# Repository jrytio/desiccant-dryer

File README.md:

# desiccant-dryer

ESPHome firmware for an ESP32 replacement of the Azco VMD-08 desiccant
air dryer control board, on a SparkFun ESP32-S2 Thing Plus or a SparkFun
Thing Plus ESP32-C6 (same sockets and wiring, one image each). Swaps packs
on measured humidity and pack
temperature instead of a fixed timer. See `CLAUDE.md` for decisions,
`docs/hardware.md` for wiring and BOM, `docs/control-logic.md` for the
state machine, `docs/virtual-testing.md` for testing without hardware,
`docs/host-preview.md` for the display on your Mac,
`docs/releasing.md` for numbered production releases and updates through Home Assistant.

Three builds share `esphome/packages/base.yaml`:

| Build | File | Sensors | Runs on |
|---|---|---|---|
| Production | `esphome/desiccant-dryer.yaml`, `esphome/desiccant-dryer-c6.yaml` | SHT45 + 3× DS18B20 (`packages/hw-real.yaml`) | ESP32-S2, ESP32-C6 |
| Hardware test | `esphome/desiccant-dryer-hw-test.yaml`, `esphome/desiccant-dryer-hw-test-c6.yaml` | Same real sensors, dev credentials and OTA | ESP32-S2, ESP32-C6 |
| Virtual | `esphome/desiccant-dryer-virtual.yaml` | On-device plant model (`packages/hw-virtual.yaml`) | ESP32-S2, nothing attached |
| Host | `esphome/desiccant-dryer-host.yaml` | Same plant model | Your Mac, display in an SDL window |
| Screen scenarios | `esphome/desiccant-dryer-scenarios.yaml` | Fixed table of twelve screen states, no controller | Your Mac; `scripts/scenario-shots.sh` renders them to `docs/display/` |

```
cp esphome/secrets.yaml.example esphome/secrets.yaml   # fill in (test builds only)
esphome run esphome/desiccant-dryer-virtual.yaml       # bare board
esphome run esphome/desiccant-dryer.yaml               # real hardware; no secrets, WiFi set at flash time
esphome run esphome/desiccant-dryer-host.yaml          # no board; brew install sdl2 first
```

CI compiles all of these on every pull request. Pushing a `vX.Y.Z` tag
(`scripts/release.sh`) publishes the production build; owners install it
once over USB with web.esphome.io, and the unit then installs later
releases itself from the published manifest, on a 6 h poll, through the
`Firmware` update entity in Home Assistant. See `docs/releasing.md`,
which also records the accepted security trade-offs of that arrangement.

## Printed circuit board

`hardware/` holds a KiCad 10 design for two fab-assembled boards: a
controller board that takes the same Thing Plus sockets and pin map, with
keyed pluggable headers, and a mains board (fuse, relays, 120 VAC plug)
behind a routed slot, joined by a keyed 4-way link. Both are generated from
Python (`scripts/hardware.sh`), checked by ERC and DRC in CI, and not yet
built. Commands, CI and ordering are in
[`hardware/README.md`](hardware/README.md); BOM, pinouts and LEDs in
`docs/hardware.md`.

## License

Copyright (C) 2026 jrytio. Released under the GNU Affero General Public
License v3.0; see [`LICENSE`](LICENSE). If you run a modified version where
others interact with it over a network (the web server, the API), the AGPL requires you to offer them your source.

Exceptions: the vendor documents in `docs/datasheets/` belong to their
manufacturers and are not covered. Release firmware also contains ESPHome's
C++ runtime (MIT), ESP-IDF (Apache 2.0) and the Barlow and Inter fonts
(SIL Open Font License 1.1), each under its own license.

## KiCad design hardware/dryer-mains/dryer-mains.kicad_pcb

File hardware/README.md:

# Hardware: the controller and mains PCBs

Two boards, generated from `dryer_board/` (see `docs/superpowers/specs/2026-10-14-pcb-design-kicad-design.md`, and its "As built" section for where the boards differ from it):

- **`dryer-controller`** (85 × 70 mm, the controller space in the enclosure): the socketed Thing Plus, 24 V in, the 5 V module, the USB-pin switch, the three MOSFET stages, the sensor and display headers, and J_RLY, the link to the mains board.
- **`dryer-mains`** (45 × 70 mm, the mains space): the fuse, the two relays with their driver stages, the 120 VAC plug, and J_CTRL, the other end of the link. The mains zone sits behind a 2 mm routed slot with four gaps for the coil tracks. Both outlines are the reviewer's enclosure sizes; the corner mounting holes (4 mm in from each edge) and the USB-C overhang (3 mm past the controller's left edge) are assumptions awaiting his confirmation; the mains plug is a vertical header inside the outline since he reported a wall beside the mains space (docs/superpowers/specs/2026-10-15-pcb-two-board-split-design.md).

The link is a JST-XH 4-way, the protoboard harness's connector and pin order: **1 = 5 V, 2 = GND, 3 = heater A, 4 = heater B**, labelled beside both headers. Pin 1 is at the top of each header with the boards side by side (controller left, mains right). The cable is 1:1, XHP-4 housing to XHP-4 housing (a pre-made "XH 2.54" 4-pin female-female lead is the same thing: XH is 2.50 mm); keep it under 30 cm. The link's 2.5 mm pitch means no other plug on either board fits it. The SHT45 is not on either board: it plugs into the Thing Plus's own Qwiic connector with a Qwiic/STEMMA QT cable (docs/hardware.md "Header pinouts").

BOM, header pinouts, LEDs, clearances and the USB-pin budget are in `docs/hardware.md` ("Printed circuit board (rev A)"); revisions and the `pcb-*` release tag in `docs/releasing.md`.

    scripts/hardware.sh env       # where KiCad was found
    scripts/hardware.sh test      # unit tests (KiCad's Python)
    scripts/hardware.sh generate [--fresh] [board]   # schematic, project, board (keeps existing tracks)
    scripts/hardware.sh route [board] [passes]       # Freerouting 2.5.0 in Docker (default 50) reroutes the SELV nets from scratch; mains copper is mains.MAINS_TRACKS
    scripts/hardware.sh check [board]                # committed files match the model; ERC; DRC
    scripts/hardware.sh export [--no-docs] [board]   # fab files and renders to hardware/out/, review copies to docs/hardware/ (--no-docs skips the copy)

Every command runs over both boards unless one is named (`controller` or `mains`). Needs KiCad 10 (`brew install --cask kicad`) and Docker for `route`. No Java.

Do not use the KiCad GUI's "Update PCB from Schematic" on these boards: the footprints carry no schematic
path, so KiCad would treat every part as new or orphaned. The generator is the update path: change
`dryer_board/`, then `generate` (and `route` if the SELV connectivity changed). The local footprints
(`dryer:*`) live in `lib/dryer.pretty` and are copied into each project's `lib/` by `generate`; edit the
copy in `lib/`, not a project's.

## Ordering (JLCPCB)

`scripts/hardware.sh export` writes, for each board, `hardware/out/dryer-<board>-rev<N>-gerbers.zip`, `-bom.csv` and `-cpl.csv`. Order the two boards as two JLCPCB orders (or one order with two files if JLCPCB offers it); each has its own BOM and CPL.

1. Upload each board's gerber zip, BOM CSV and CPL CSV to JLCPCB.
2. Options: 2 layers, 1.6 mm, 1 oz copper, HASL lead-free, assembly on the top side.
3. Run JLCPCB's DFM analysis on the uploaded gerbers before paying.
4. In JLCPCB's placement preview, check every polarised and keyed part before paying. The CPL is already written for JLCPCB: each part's position is the centre of its pads (KiCad's own position file gives the footprint anchor, which is pin 1 on the connectors, sockets, relays, fuse holder, switch and U1, so those appeared shifted by half a body in the first upload on 2026-10-16), and the rotations carry the per-package corrections in `JLC_ROTATIONS` in `hardware/dryer_board/export.py` (pluggable headers and the XH links 180°, 1×N pin sockets and headers −90°, SOT-23 180°, electrolytics 180°, SMA diodes 180°, 0805 LEDs 180°; resistors, ceramics and the PPTC unchanged). The connector, socket, SOT-23 and electrolytic values match that preview; the SMA diodes, the LEDs, the direction of the pin-socket turn (pin 1 at the USB end), the relays, the fuse holder and the slide switch are set by analogy or left at KiCad's angle and must be confirmed in the preview. If one is off, change its entry in `JLC_ROTATIONS`, run `scripts/hardware.sh export`, re-upload the CPL and look again; do not fix it only in the browser, or the next export loses it. The flyback diodes D5 to D7 and the 24 V diodes D11 and D14 matter most: reversed, a flyback shorts its output when it switches on. JLCPCB's 3D review draws a flat box over the footprint for any part its library has no 3D model for; the fuse holder (XFCN PTF-76-B, C48603682) is one of them (seen 2026-10-16: JLCPCB's part page lists an EasyEDA footprint and no model). That is not an error: check the part in the 2D view instead (two pads 15 mm apart, 1.6 mm holes, body outline 24.4 × 9.4 mm, which is what XFCN's drawing gives) and that the BOM step matched it to C48603682 with through-hole assembly on.
5. The minimum order is five boards of each.
6. Every fab-fitted part carries its LCSC number in the BOM (`hardware/dryer_board/controller.py` and `mains.py`; each part's description says basic or extended). JLCPCB charges a per-part loading fee for each extended part: the relays, the MOSFETs, the electrolytics, the PPTC, the fuse holder, the headers and sockets, the two XH link headers and the switch.
7. **U1 (the 5 V module, controller board) is hand-fitted.** It is in the BOM with no LCSC number, so deselect it in JLCPCB's BOM check. The footprint is drawn for the TRACO TSR 1-2450 (Mouser 495-TSR-1-2450). The Amazon-listed "AOTUPASION TSR 1-2450" (B0GTTJ4PNX) fits it mechanically: 11.5 × 7.5 × 10 mm body inside the footprint's 11.7 × 7.6 outline, three SIP pins on the 2.54 mm pitch, and the pin-1 dot at the same end as TRACO's drawing. The listing does not state its pinout and the label carries no TRACO logo, so **before soldering one, power it on the bench: current-limited 12 V on pin 1 (+) and pin 2 (GND), expect 5 V on pin 3** (docs/board-continuity-check.md, PCB item 0). A MornSun K7805-1000R3 from another distributor also fits (same pinout).
8. **F1 (the fuse holder, mains board) is fab-fitted**: the XFCN PTF-76-B covered holder (LCSC C48603682, 15 mm pitch, UL 250 VAC 20 A), the single-board rev A's choice. The covered 5 × 20 mm holders on hand (Amazon B0FCS5MK1Y, the BLX-A moulding; the reviewer confirmed their pitch at about 22 mm on 2026-10-15, after a first reading of 12.5 mm from the listing's picture) are **not fitted**: with mains copper 1 mm from the slot, their 25.8 mm body would run from x 10.35 to 36.15 and into the vertical plug (strip, slot, clearance, holder and the plug's body add up to 45.6 mm across the 45 mm board; 1 mm over against the plug's courtyard). The `Fuseholder_5x20mm_Covered_P22.50mm_Slot` footprint stays in `lib/dryer.pretty` for a right-angle-plug layout, where they fit. The 5 × 20 mm fuse itself (T 3.15 A) is bought separately. First-article note: the plug's pin-1 wires leave 2 to 4 mm from the holder's lift-off cap, so changing the fuse may need the plug pulled first (unverified until a board is built).
9. The mating plugs for the pluggable headers, and the link cable, are not on the boards. Order them as loose parts (LCSC numbers; DORABO screw plugs, green):

   | Header | Plug | LCSC |
   |---|---|---|
   | J_MAINS (8-pin 5.08 mm, mains board; the header is the vertical DB2EV-5.08-8P-GN, C395787, since the reviewer reported a wall beside the mains space) | DB2EK-5.08-8P-GN-S | C395791 |
   | J_LOADS (6-pin 5.08 mm, controller) | DB2EK-5.08-6P-GN-S | C395774 |
   | J_24V (2-pin 5.08 mm, controller) | DB2EK-5.08-2P-GN-S | C395732 |
   | J_SENS (9-pin 3.5 mm, controller) | DB2EK-3.5-9P-GN-S | C430561 |
   | J_RLY and J_CTRL (JST XH 4-way, one each board) | 2 × XHP-4 housing + 8 × SXH-001T-P0.6 crimps and a 4-core lead, or a pre-made 4-pin XH female-female cable | JST, any distributor |

   The mounting holes on both boards are 4.3 mm, for M4 hardware.

### PCBWay instead of JLCPCB

Both boards can be fabricated and assembled by PCBWay with no design change: the gerbers, drill files and footprints are standard, and PCBWay assembles through-hole parts and accepts DNP lines (U1 and F1). What changes is the paperwork and the sourcing, not the boards:

- PCBWay wants its own BOM columns (line, quantity, designators, manufacturer, MPN, description, package, SMT/PTH, and a distributor part number) rather than JLCPCB's four; the LCSC numbers go in the distributor column. Their centroid file is the same designator / X / Y / rotation / side list as the CPL.
- PCBWay sources from Digi-Key, Mouser, Farnell, Arrow, Avnet and "local suppliers", and will buy from a supplier or link you name in the BOM, with substitutes only on your approval. Whether they buy from LCSC was not confirmed on their pages. The parts at risk are the LCSC-only Chinese brands: the DORABO pluggable headers and plugs, the Kinghelm sockets, the SOFNG slide switch, the XFCN display header, and the Songle relays (not at Digi-Key; a TE equivalent would need its pin pattern checked). The passives, LEDs, diodes, transistors and electrolytics are generic and have Western-distributor equivalents in the same footprints.
- Practical route if PCBWay is chosen: order it as a kitted or combo job, buy the LCSC-only parts yourself (with spares, PCBWay asks for extra passives) and ship them, or put the LCSC links in the BOM and get the all-in quote in writing before paying. PCBWay's MOQ is 1 (the quote form starts at 5); the online price excludes parts and the exact quote follows a manual review in one to two days.

#### Quote packet (2026-10-16)

Everything PCBWay's quote form asks for, so the request takes a few minutes. The request itself needs a PCBWay account and contact details, so a person files it (the hardware reviewer asked for an estimate on PR #49).

Files: the `hardware-outputs` artifact of the latest green [hardware workflow run](https://github.com/jrytio/desiccant-dryer/actions/workflows/hardware.yml) on the PR branch (or `scripts/hardware.sh export` locally, into `hardware/out/`): `dryer-controller-revA-gerbers.zip` and `dryer-mains-revA-gerbers.zip` (gerbers and drill files, one zip per board), `dryer-*-revA-bom.csv` (JLCPCB columns: comment, designators, footprint, LCSC number; PCBWay accepts it, the LCSC number is the distributor part number), `dryer-*-revA-cpl.csv` (centroids, top side; positions are the pad centres and the rotations follow JLCPCB's library orientations per item 4 above, so PCBWay's reviewers must check orientation in their own preview) and `dryer-*-revA-schematic.pdf`.

| | Controller board | Mains board |
|---|---|---|
| Size | 85 × 70 mm | 45 × 70 mm |
| Layers, material, thickness, copper | 2, FR-4, 1.6 mm, 1 oz | same |
| Surface finish | lead-free HASL (ENIG if preferred; nothing in the design needs it) | same |
| Min track / clearance | 0.2 / 0.2 mm (0.225 mm is the narrowest track routed) | same |
| Min hole | 0.3 mm via drill; smallest part hole 0.95 mm | same; 1.6 mm fuse-holder holes |
| Cutouts | none | one 2 mm wide routed slot in five segments (internal cutouts, in the Edge.Cuts layer) |
| Mounting holes | 4 × 4.3 mm non-plated | same |
| Quantity | 5 (the form's minimum; 2 to 5 are wanted) | 5 |
| Assembly | top side only, SMD and through-hole: 26 BOM lines, 43 placements (34 SMD, 9 through-hole: the two ESP sockets, five pluggable headers, the slide switch, U1). U1 (the 5 V module) is hand-fitted: mark it DNP / "do not source" | top side only: 9 BOM lines, 15 placements (10 SMD, 5 through-hole: fuse holder, two relays, two headers). Nothing excluded |
| Parts to confirm sourcing | the LCSC-only brands (see above); the DORABO headers (J_LOADS C395768, J_24V C395734, J_SENS C430559, J_RLY JST C144395 is generic) | DORABO DB2EV-5.08-8P-GN C395787, XFCN PTF-76-B C48603682, Songle SRD-05VDC-SL-C C35449, JST C144395 |

Steps on pcbway.com: PCB Instant Quote → enter the table (one quote per board, or both in one order as two parts) → tick "Assembly" and give the placement counts → upload the two zips, the BOMs and the CPLs → "Request a quote". Expect the manual review to ask about the mains board's slot (it is intentional, an isolation slot) and about sourcing the Chinese-brand parts.

## CI

`.github/workflows/hardware.yml` runs `test`, `check` and `export --no-docs` in the `kicad/kicad:10.0.6` image (pinned to the patch release the TP2 placement was checked against; amd64 only; on Apple silicon use `docker run --platform linux/amd64 -u $(id -u):$(id -g) -e HOME=/tmp`). It never routes. `hardware/out/` is uploaded as an artifact and the review copies in `docs/hardware/` (`controller-*`, `mains-*`) are not touched, so they change only when someone runs `export` locally. A `pcb-*` tag attaches both boards' gerber zips, BOMs, CPLs and schematic PDFs to a GitHub release.

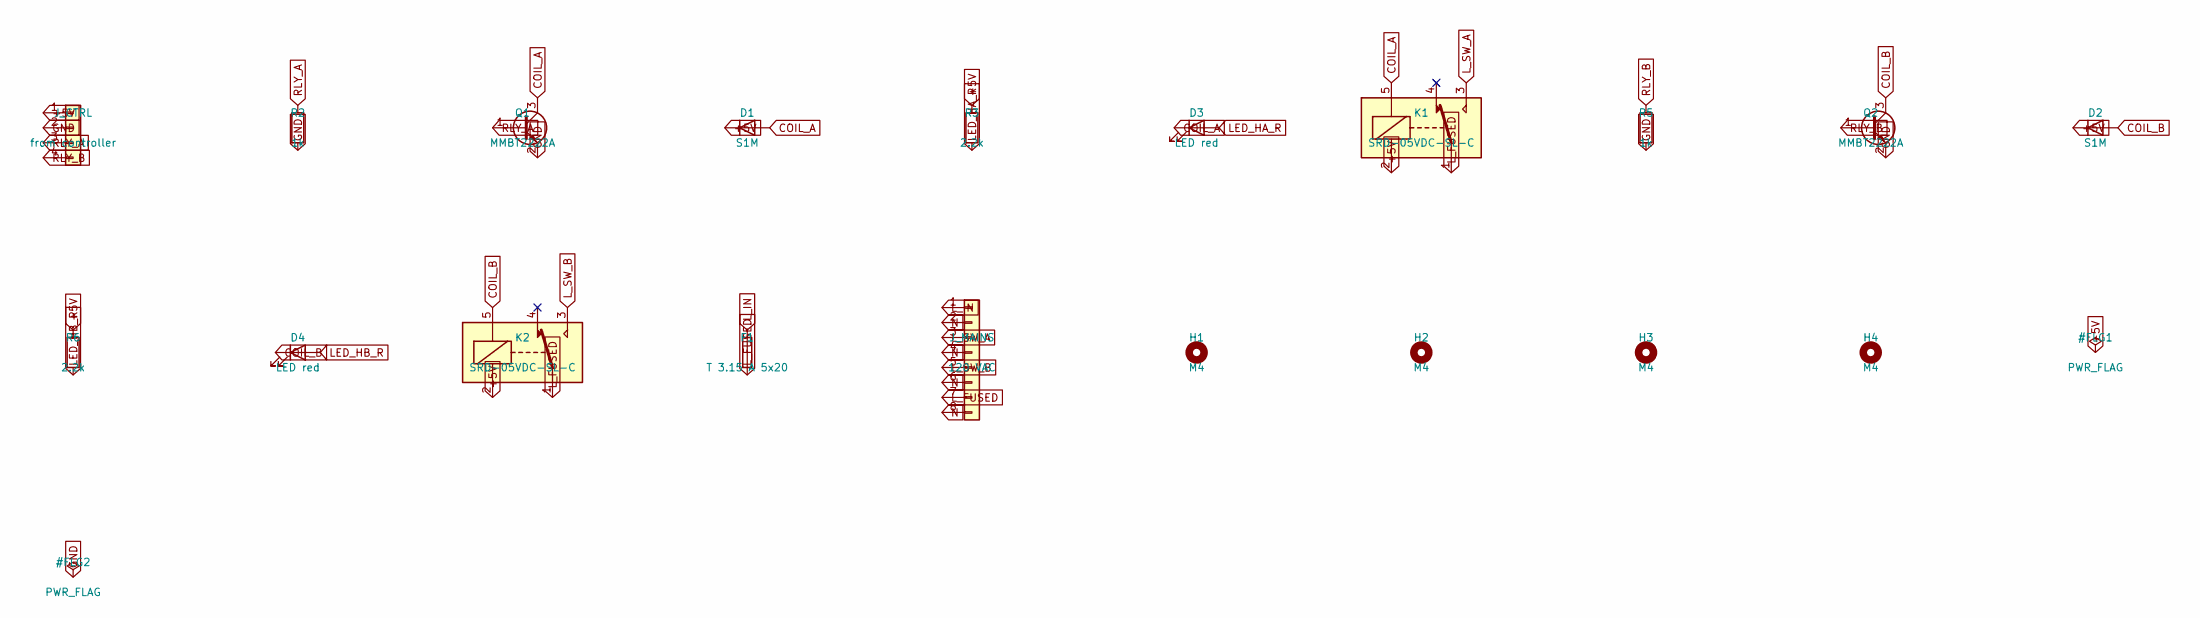
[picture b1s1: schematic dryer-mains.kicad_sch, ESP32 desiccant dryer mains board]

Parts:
D1, D2: S1M; D_SMA; LCSC C95872
D3, D4: LED red; LED_0805_2012Metric; LCSC C84256
F1: T 3.15 A 5x20; Fuseholder_5x20mm_Covered_P12.50mm_Slot
H1, H2, H3, H4: M4; MountingHole_4.3mm_M4
J_CTRL: from controller; JST_XH_B4B-XH-A_1x04_P2.50mm_Vertical; LCSC C144395
J_MAINS: 120 VAC; PhoenixContact_MSTBVA_2,5_8-G-5,08_1x08_P5.08mm_Vertical_Dr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; LCSC C395787
K1, K2: SRD-05VDC-SL-C; Relay_SPDT_SANYOU_SRD_Series_Form_C; LCSC C35449
Q1, Q2: MMBT2222A; SOT-23; LCSC C8512
R2, R5: 1k; R_0805_2012Metric; LCSC C17513
R3, R6: 2.2k; R_0805_2012Metric; LCSC C17520

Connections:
+5V: D1.1 (K), D2.1 (K), J_CTRL.1, K1.2, K2.2, R3.1, R6.1
COIL_A: D1.2 (A), D3.1 (K), K1.5, Q1.3 (C)
COIL_B: D2.2 (A), D4.1 (K), K2.5, Q2.3 (C)
GND: J_CTRL.2, Q1.2 (E), Q2.2 (E), R2.2, R5.2
LED_HA_R: D3.2 (A), R3.2
LED_HB_R: D4.2 (A), R6.2
L_FUSED: F1.2, J_MAINS.7, K1.1, K2.1
L_IN: F1.1, J_MAINS.1
L_SW_A: J_MAINS.3, K1.3
L_SW_B: J_MAINS.5, K2.3
N: J_MAINS.2, J_MAINS.4, J_MAINS.6, J_MAINS.8
RLY_A: J_CTRL.3, Q1.1 (B), R2.1
RLY_B: J_CTRL.4, Q2.1 (B), R5.1

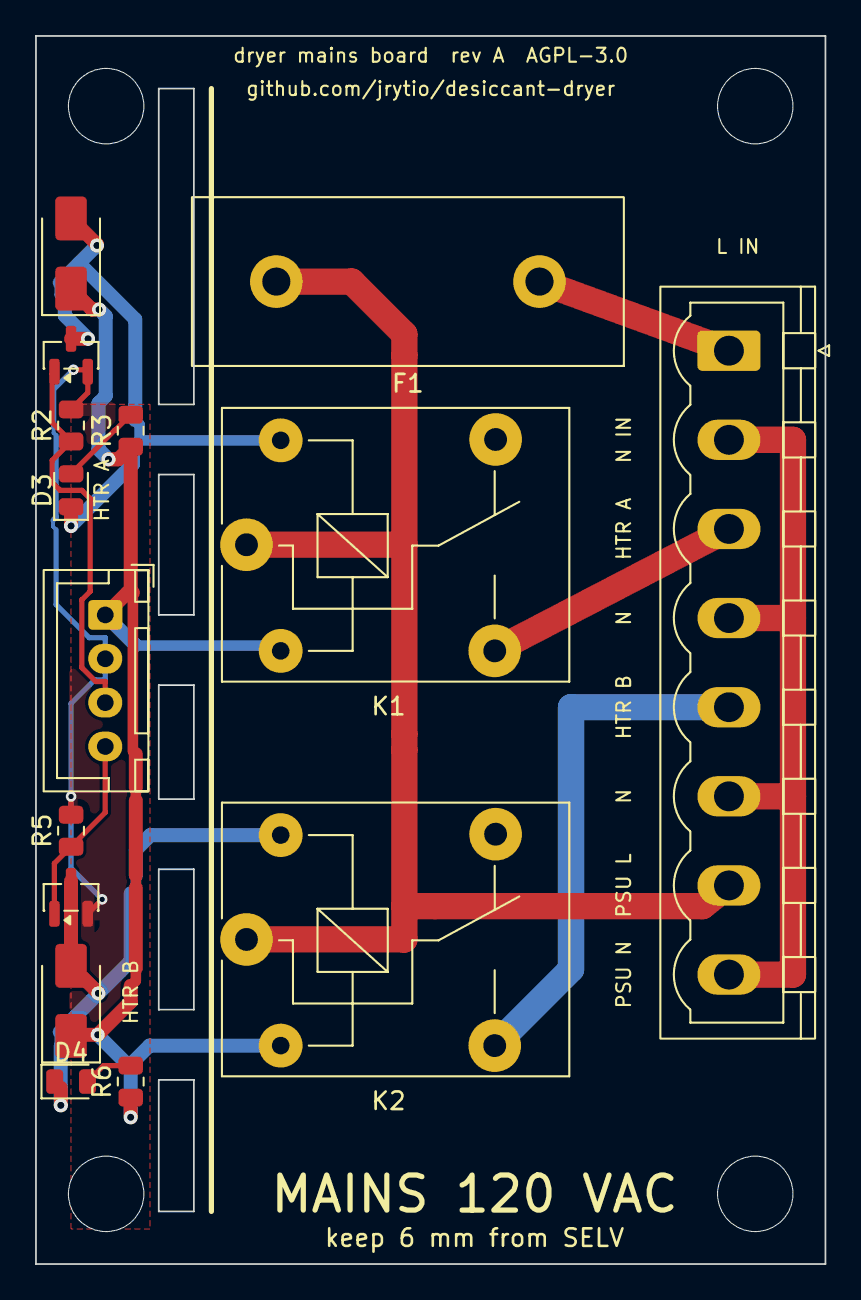
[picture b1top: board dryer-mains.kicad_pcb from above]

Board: 2 copper layers, 45.0 x 70.0 mm, 19 parts (0 on the bottom side), 13 nets.

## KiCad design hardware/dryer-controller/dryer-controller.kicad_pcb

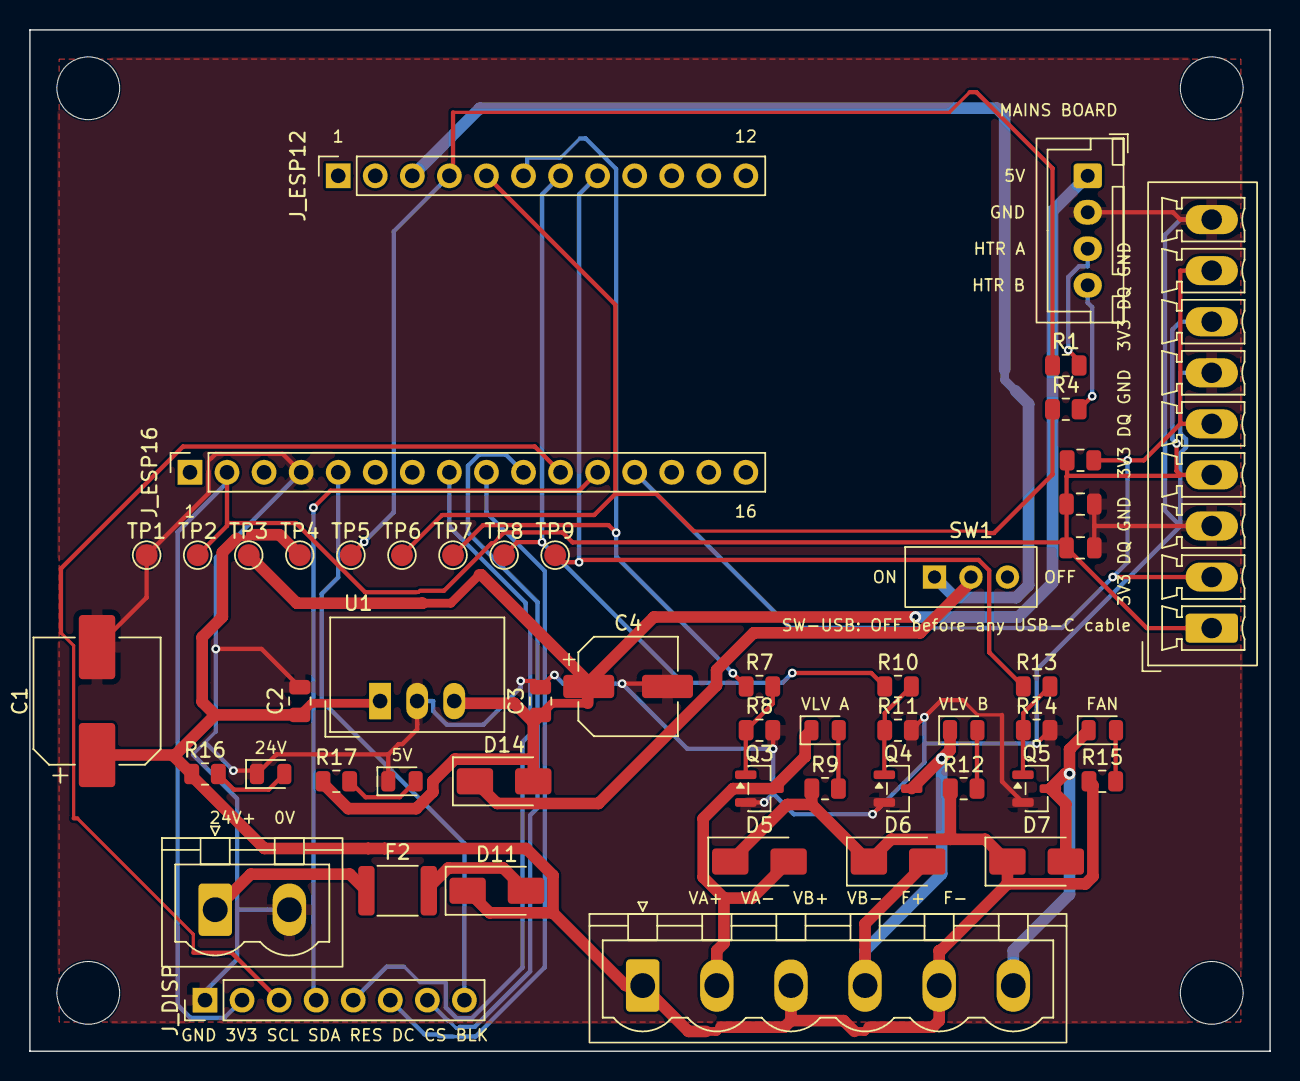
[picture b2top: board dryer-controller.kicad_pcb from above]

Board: 2 copper layers, 85.0 x 70.0 mm, 56 parts (0 on the bottom side), 33 nets.

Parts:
C1: 100u 50V; CP_Elec_8x10.5
C2: 10u 50V; C_0805_2012Metric
C3: 22u 10V; C_0805_2012Metric
C4: 100u 16V; CP_Elec_6.3x7.7
C5: 100n; C_0805_2012Metric
C6: 10u 10V; C_0805_2012Metric
D5, D6, D7: S1M; D_SMA
D8, D9, D10: LED yellow; LED_0805_2012Metric
D11, D14: SS34; D_SMA
D12, D13: LED green; LED_0805_2012Metric
F2: PPTC 1.1 A 30 V; Fuse_1812_4532Metric
H1, H2, H3, H4: M4; MountingHole_4.3mm_M4
J_24V: 24 V in; PhoenixContact_MSTBVA_2,5_2-G-5,08_1x02_P5.08mm_Vertical_Dr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
J_DISP: ST7789 240x240; PinHeader_1x08_P2.54mm_Vertical
J_ESP12: Thing Plus 12-pin; PinSocket_1x12_P2.54mm_Vertical
J_ESP16: Thing Plus 16-pin; PinSocket_1x16_P2.54mm_Vertical
J_LOADS: valves + fan; PhoenixContact_MSTBVA_2,5_6-G-5,08_1x06_P5.08mm_Vertical_Dr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
J_RLY: to mains board; JST_XH_B4B-XH-A_1x04_P2.50mm_Vertical
J_SENS: DS18B20 x3; PhoenixContact_MCV_1,5_9-G-3.5_1x09_P3.50mm_Vertical_Drill1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
Q3, Q4, Q5: CJ2310; SOT-23
R1, R4: 1k; R_0805_2012Metric
R7, R10, R13: 100; R_0805_2012Metric
R8, R9, R11, R12, R14, R15, R16: 10k; R_0805_2012Metric
R17: 2.2k; R_0805_2012Metric
R18: 5.1k; R_0805_2012Metric
SW1: SW-USB; SW_Slide_SPDT_SOFNG_SS-12D00_P2.50mm
TP1: GND; TestPoint_Pad_D1.5mm
TP2: 3V3; TestPoint_Pad_D1.5mm
TP3: 5V; TestPoint_Pad_D1.5mm
TP4: 24V; TestPoint_Pad_D1.5mm
TP5: HTR_A; TestPoint_Pad_D1.5mm
TP6: HTR_B; TestPoint_Pad_D1.5mm
TP7: VLV_A; TestPoint_Pad_D1.5mm
TP8: VLV_B; TestPoint_Pad_D1.5mm
TP9: FAN; TestPoint_Pad_D1.5mm
U1: TSR 1-2450; Converter_DCDC_TRACO_TSR-1_THT

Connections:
+3V3: C5.1, C6.1, J_DISP.2, J_ESP16.2, J_SENS.1, J_SENS.4, J_SENS.7, R18.1, TP2.1
+5V: C3.1, C4.1, D14.2, J_RLY.1, R17.1, TP3.1, U1.3
+24V: C1.1, C2.1, D5.1, D6.1, D7.1, D11.1, J_LOADS.1, J_LOADS.3, J_LOADS.5, R9.1, R12.1, R15.1, R16.1, TP4.1, U1.1
+24V_F: D11.2, F2.2
+24V_RAW: F2.1, J_24V.1
FAN: J_ESP12.8, R13.1, TP9.1
GATE_A: Q3.1, R7.2, R8.1
GATE_B: Q4.1, R10.2, R11.1
GATE_C: Q5.1, R13.2, R14.1
GND: C1.2, C2.2, C3.2, C4.2, C5.2, C6.2, D12.1, D13.1, J_24V.2, J_DISP.1, J_ESP16.4, J_RLY.2, J_SENS.3, J_SENS.6, J_SENS.9, Q3.2, Q4.2, Q5.2, R8.2, R11.2, R14.2, TP1.1, U1.2
HTR_A: J_ESP12.4, R1.1, TP5.1
HTR_B: J_ESP12.5, R4.1, TP6.1
LCD_BL: J_DISP.8, J_ESP16.5
LCD_CS: J_DISP.7, J_ESP16.10
LCD_DC: J_DISP.6, J_ESP16.9
LCD_RST: J_DISP.5, J_ESP16.8
LED_5V_R: D13.2, R17.2
LED_24V_R: D12.2, R16.2
LED_FAN_R: D10.2, R15.2
LED_VA_R: D8.2, R9.2
LED_VB_R: D9.2, R12.2
OW_DQ: J_ESP16.13, J_SENS.2, J_SENS.5, J_SENS.8, R18.2
RLY_A: J_RLY.3, R1.2
RLY_B: J_RLY.4, R4.2
SPI_CLK: J_DISP.3, J_ESP16.11
SPI_MOSI: J_DISP.4, J_ESP16.12
SW_FAN: D7.2, D10.1, J_LOADS.6, Q5.3
SW_VA: D5.2, D8.1, J_LOADS.2, Q3.3
SW_VB: D6.2, D9.1, J_LOADS.4, Q4.3
V5_D: D14.1, SW1.2
VBUS: J_ESP12.3, SW1.1
VLV_A: J_ESP12.6, R7.1, TP7.1
VLV_B: J_ESP12.7, R10.1, TP8.1

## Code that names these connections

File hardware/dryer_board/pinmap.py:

# hardware/dryer_board/pinmap.py
"""Header position -> function, the wiring the main board commits to. The GPIO behind a
position differs per Thing Plus and lives in esphome/packages/board-*.yaml; tests/test_pinmap.py
holds both against each other. Source: docs/pinout-verification.md."""

# function: (header pin count, position counted from the USB end)
FUNCTIONS = {
    "usb_5v":    (12, 3),
    "heater_a":  (12, 4),
    "heater_b":  (12, 5),
    "valve_a":   (12, 6),
    "valve_b":   (12, 7),
    "fan":       (12, 8),
    "i2c_scl":   (12, 11),   # Qwiic; not wired on the main board
    "i2c_sda":   (12, 12),   # Qwiic; not wired on the main board
    "3v3":       (16, 2),
    "gnd":       (16, 4),
    "lcd_bl":    (16, 5),
    "lcd_rst":   (16, 8),
    "lcd_dc":    (16, 9),
    "lcd_cs":    (16, 10),
    "spi_clk":   (16, 11),
    "spi_mosi":  (16, 12),
    "onewire":   (16, 13),
}

# Positions that must stay unconnected because a board gives them a job.
RESERVED = {(12, 9): "C6 RGB LED data", (12, 10): "C6 boot strap GPIO15",
            (16, 15): "C6 UART0 TX", (16, 16): "C6 BOOT strap GPIO9",
            (16, 1): "ESP reset", (12, 2): "LDO enable", (12, 1): "battery"}

# position -> GPIO, per board, from docs/pinout-verification.md
POSITION_GPIO = {
    "s2": {(16, 5): 17, (16, 8): 9, (16, 9): 7, (16, 10): 5, (16, 11): 36, (16, 12): 35, (16, 13): 37,
           (12, 4): 13, (12, 5): 12, (12, 6): 11, (12, 7): 10, (12, 8): 8, (12, 11): 2, (12, 12): 1},
    "c6": {(16, 5): 0, (16, 8): 3, (16, 9): 4, (16, 10): 5, (16, 11): 19, (16, 12): 20, (16, 13): 21,
           (12, 4): 18, (12, 5): 22, (12, 6): 11, (12, 7): 10, (12, 8): 8, (12, 11): 7, (12, 12): 6},
}

# firmware substitution name -> function
SUBSTITUTIONS = {"pin_heater_a": "heater_a", "pin_heater_b": "heater_b", "pin_valve_a": "valve_a",
                 "pin_valve_b": "valve_b", "pin_fan": "fan", "pin_i2c_sda": "i2c_sda", "pin_i2c_scl": "i2c_scl",
                 "pin_onewire": "onewire", "pin_spi_clk": "spi_clk", "pin_spi_mosi": "spi_mosi",
                 "pin_lcd_cs": "lcd_cs", "pin_lcd_dc": "lcd_dc", "pin_lcd_rst": "lcd_rst", "pin_lcd_bl": "lcd_bl"}

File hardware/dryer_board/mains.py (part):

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#   edge to the Edge.Cuts stroke), so the pads cannot go further right. The vertical body is
#   deeper on one side of its pin row (5.34 mm) than the other (4.34); rotation 270 puts the
#   deep side toward the edge, courtyard x 35.16 to 44.84, y 13.86 to 57.58, between F1 and
#   H4's courtyard (from y 61.4). Pin 1 at the top keeps L_SW_A (pin 3) and L_SW_B (pin 5) from
#   crossing: K1's contact feeds the upper pin and K2's the lower.
# - F1 at (28.7, 14) rotated 180: the XFCN PTF-76-B body (24.4 mm, pins 4.7 mm from each end)
#   sits at x 9.0 to 33.4 from the slot edge, courtyard 8.75 to 33.65, 1.5 mm short of
#   J_MAINS's (x 35.16). The rotation puts pad 1 (L_IN) on the plug side at x 28.7, a short
#   diagonal from pin 1, and pad 2 (L_FUSED) at x 13.7 beside the strip, its copper (x 12.2
#   up) 3.2 mm from the slot; the courtyard top (y 9.05) clears H1's and H2's (to y 8.6). The
#   BLX-A holders on hand do not fit here: pad copper 1 mm from the slot puts their 25.8 mm
#   body at x 10.35 to 36.15, into the plug (the 22.5 mm slotted footprint stays in the
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#   15.2) is the mains copper nearest the strip outside an area: 6.3 mm above K1's top coil
#   pad, 9 mm from the strip's parts (test_margins.py prints the minimum). The spine's short
#   pieces between the areas are 6.5 mm from the coil pads;
# - 6 mm hole clearance from the M4 holes (H2 at (41, 4): the plug's pin 1 and the L_IN
#   diagonal to it are the closest mains copper, about 10 mm from the hole's edge);
# - 1 mm between mains nets (the NC pads are mains). L to N 1.10 mm (the rule is 1.0; the
#   single board had 1.55; regaining it would put the N links at the edge's 1 mm limit): the N
#   links beside the plug pins. The L-side nets keep 1.6 mm from each other (RULES): the
#   L_FUSED branch to pin 7 passes K2's NC pad at 1.85, L_SW_B's lane passes K2's NC pad at
#   2.05;
# - 1 mm to the board edge: the N links at x 43.15 are 1.05 mm from it (copper edge);
# - the relay_pads relaxation (3.5 mm) applies to a whole segment if any of it touches a relay
#   area (insideArea tests the item, not the overlapping part), so every segment that would cross
#   an area edge is split there: the x 21 spine at y 18.2 and 39.8/40.7 (the pieces outside
#   end 0.75 mm, a cap, short of the areas, y 19-39 and 41.5-61.5), the L_FUSED branch to pin 7
#   at x 22.75, so no mains segment outside an area is relaxed.
# The spine at x 21 carries L_FUSED on F.Cu between the coil pads (x <= 13.95 + 1.25) and the
# NC/NO pads, from F1's pad 2 down to both COM pads, with a branch at y 49.6 to J_MAINS pin 7
# (PSU L). L_IN is one short diagonal from F1's pad 1, on the plug side, to pin 1 at the top
# of the plug. N links the four N pins on the edge side of J_MAINS.
# The switched lines reach pins 3 and 5 from the left: L_SW_A straight from K1's NO pad on
# F.Cu, L_SW_B from K2's NO pad up the x 30.5 lane on B.Cu (it crosses under the pin-7 branch).
MAINS_TRACKS = [
    ("L_IN", "F.Cu", [(28.7, 14), (39.5, 17.94)]),
    ("L_FUSED", "F.Cu", [(13.7, 14), (18, 14), (21, 17), (21, 18.2), (21, 39.8), (21, 40.7), (21, 51.5), (12, 51.5)]),
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

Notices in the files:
hardware/dryer-controller/dryer-controller.kicad_pcb:
ESP32 desiccant dryer controller  rev A  AGPL-3.0  github.com/jrytio/desiccant-dryer
hardware/dryer-mains/dryer-mains.kicad_pcb:
dryer mains board  rev A  AGPL-3.0
